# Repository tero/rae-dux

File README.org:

* rae-dux
| [[images/board-front.png]] | [[images/board-back.png]] |

The rae-dux is a 36-key (diodeless!), wireless keyboard inspired by the [[https://github.com/tapioki/cephalopoda/tree/main/Architeuthis%20dux][Architeuthis Dux]].
This project used to use the [[https://github.com/soundmonster/samoklava][samoklava workflow]], however the auto-router had
troubles with the splay, currently I just use the image generating parts of the
samoklava workflow.

*This has now been printed and is working perfectly with ZMK!*
The ZMK shield can be found [[https://github.com/andrewjrae/zmk-config/tree/development/config/boards/shields/rae_dux][here]], as far as I can tell small custom projects
like this aren't to be merged into ZMK main, so you'll have to emulate what I'm
doing in my =zmk-config= [[https://github.com/andrewjrae/zmk-config/tree/development/config][here]].

** Build Guide
The wonderful @tzcl created a [[https://www.tzcl.me/blog/rae-dux][build guide]] for the rae-dux, so if you are curious
about building the board, but don't have experience with this sort of thing go
check it out!

** Important Notes
- *Wireless only*, the 36-key diodeless approach uses the P0 pin which is usually dedicated to TRRS
- Since I ended up largely ditching the samoklava workflow, *the actions page with gerbers is out of date and no longer relevant**
- Their is only one MCU footprint, so *one controller has to be flipped* (I assume
   if you can get this printed you can figure out the correct orientation)
- The [[./rae-dux.yaml][rae-dux.yaml]] file relies on [[https://github.com/andrewjrae/ergogen/tree/rae-dux][my fork of ergogen]] which naturally relies on
  [[https://github.com/soundmonster/ergogen/tree/samoklava][soundmonster's fork of ergogen]], and a simple JST battery footprint inspired by
  [[https://github.com/benvallack][@benvallack]].
- If you want to skip out on the switch, there is no jumper to use the JST
  connector, so you'll have to bodge a wire somewhere, or try shorting the
  switch footprint.
- Kicad files are 6.0, so unfortunately not backwards compatible.

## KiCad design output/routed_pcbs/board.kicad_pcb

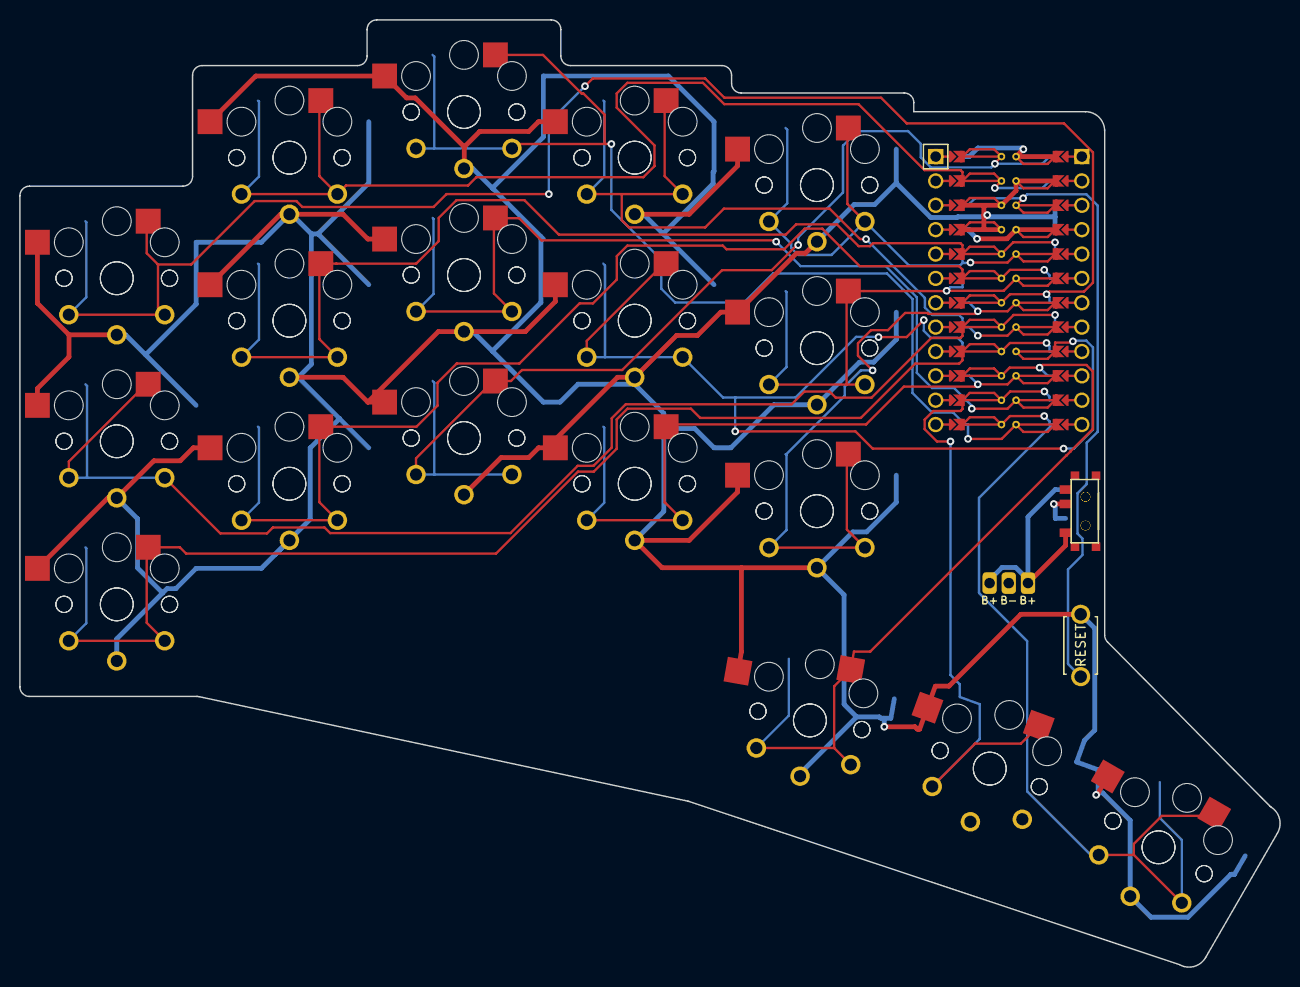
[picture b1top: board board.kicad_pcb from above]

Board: 2 copper layers, 131.4 x 98.8 mm, 41 parts (0 on the bottom side), 22 nets.

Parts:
B1: ResetSW
MCU1: ProMicro
PAD1: bat
S1, S2, S3, S4, S5, S6, S7, S8, S9, S10, S11, S12, S13, S14, S15, S16, S17, S18, S19, S20, S21, S22, S23, S24, S25, S26, S27, S28, S29, S30, S31, S32, S33, S34, S35, S36: PG1350
T1, T2: SPDT_C128955

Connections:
Bplus: T1.2, T2.2
Braw: PAD1.1, T1.1, T2.1
GND: B1.2, MCU1.2, MCU1.21, MCU1.22, S1.2, S2.2, S3.2, S4.2, S5.2, S6.2, S7.2, S8.2, S9.2, S10.2, S11.2, S12.2, S13.2, S14.2, S15.2, S16.2, S17.2, S18.2, S19.2, S20.2, S21.2, S22.2, S23.2, S24.2, S25.2, S26.2, S27.2, S28.2, S29.2, S30.2, S31.2, S32.2, S33.2, S34.2, S35.2, S36.2
P0: MCU1.23, S11.1, S12.1
P1: MCU1.24, S13.1, S14.1
P2: MCU1.20, S9.1, S10.1
P3: MCU1.19, S7.1, S8.1
P4: MCU1.18, S5.1, S6.1
P5: MCU1.17, S3.1, S4.1
P6: MCU1.16, S1.1, S2.1
P7: MCU1.15, S31.1, S32.1
P8: MCU1.14, S33.1, S34.1
P9: MCU1.13, S35.1, S36.1
P10: MCU1.12, S17.1, S18.1
P14: MCU1.10, S19.1, S20.1
P15: MCU1.9, S21.1, S22.1
P16: MCU1.11, S15.1, S16.1
P18: MCU1.8, S23.1, S24.1
P19: MCU1.7, S25.1, S26.1
P20: MCU1.6, S27.1, S28.1
P21: MCU1.5, S29.1, S30.1
RST: B1.1, MCU1.3

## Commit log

2022-01-05 Using my fork of soundmonster's fork of ergogen.
2022-01-05 Part way done, auto-routing currently isn't completing.
2022-01-06 Shaping completed, autorouting still not converging
2022-01-06 Fixing autorouting by ensuring the MCU footprint isn't rotated.
2022-01-07 Reverting the redirecting to my fork of ergogen.
2022-01-07 Renaming to rae-dux and fixing build flows.
2022-01-07 Adding new readme.
2022-01-07 Fleshing out readme.
2022-01-07 Fixing readme typos.
2022-01-16 Starting to move towards a diodeless solution option, no more autorouting :(
2022-01-16 Adding diodeless build, requires routing.
2022-01-16 Turns out autoroute works! It ain't pretty though.
2022-01-16 Revert "Turns out autoroute works! It ain't pretty though." - I lied...
    This reverts commit cc5cec8c6c869663a139bc6d900cc8c8e3186058.
2022-01-16 Added routed board, but the switch isn't actually functional... unless you solder directly to it.
2022-01-16 forgot to add board routed pro file
2022-01-16 Fixing typo in gen_images
2022-01-17 Adding new style for pcbdraw
2022-01-17 Adding battery footprint, and pointing to my new ergogen fork.
    Still require routing.
2022-01-17 Routed new design with battery connectors.
2022-01-17 Updating gitignore
2022-01-17 Cleaning up board a little.
2022-01-18 Updating readme.
2022-01-18 Adding bold for the truly important bits ;)
2022-01-18 Cleaning up the board even more.
2022-01-21 Increasing pinky stagger and fixing battery footprint to actually work with JST PH (fixed upstream in ergogen fork).
2022-01-21 Finished routing the latest revision.
2022-03-21 Updating readme
2022-03-27 Adding gerber and updating readme.
2022-04-02 Fixing errors.
2022-09-24 Finally adding build guide link!
2022-09-29 updated layout with less rotation
2022-11-07 add latest output
2022-11-07 add DS_Store to gitignore
2022-11-07 use new fork of ergogen that includes promicro_pretty
2022-11-07 update rae-dux.yaml with promicro_pretty and slight changes to pin mapping
